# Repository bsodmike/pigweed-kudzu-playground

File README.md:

# Kudzu

[TOC]

## Getting Started

Make sure you've set up [Pigweed's
prerequisites](https://pigweed.dev/docs/getting_started.html#prerequisites).

**If you're on Windows**, you can automate the initial setup by downloading the
first-time setup script **from cmd.exe**:

```bat
curl https://pigweed.googlesource.com/pigweed/sample_project/+/main/tools/setup_windows_prerequisites.bat?format=TEXT > setup_pigweed_prerequisites.b64 && certutil -decode -f setup_pigweed_prerequisites.b64 setup_pigweed_prerequisites.bat && del setup_pigweed_prerequisites.b64
```

Then you can run the script with the following command **in cmd.exe**:

```bat
setup_pigweed_prerequisites.bat
```

Note: You may see a few UAC prompts as the script installs Git, Python, and
enables developer mode.

Once that is done, you can clone this project with the following command:
```sh
git clone https://pigweed.googlesource.com/pigweed/kudzu
```

### Environment setup

Pigweed uses a local development environment for most of its tools. This
means tools are not installed to your machine, and are instead stored in a
directory inside your project (Note: git ignores this directory). The tools
are temporarily added to the PATH of the current shell session.

To make sure the latest tooling has been fetched and set up, run the bootstrap
command for your operating system:

**Windows**

```bat
bootstrap.bat
```

**Linux & Mac**

```sh
source ./bootstrap.sh
```

After tooling updates, you might need to run bootstrap again to ensure the
latest tools.

After the initial bootstrap, you can use use the `activate` scripts to configure
the current shell for development without doing a full update.

**Windows**

```sh
activate.bat
```

**Linux & Mac**

```sh
source ./activate.sh
```

### Device tools setup

Install the pico SDK and tool to flash the device.

```sh
pw package install pico_sdk
pw package install picotool
```
These packages will be built and added to the path automatically. There is no
need to add these to the gn arguments.

## Linux Setup

### GLFW Dependency:

Install the GLFW OpenGL library
```sh
sudo apt install libglfw3-dev libglfw3
```

### Udev Rules:

Put the following into `/usr/lib/udev/rules.d/49-picoprobe.rules`

```
# Pico app mode
SUBSYSTEMS=="usb", ATTRS{idVendor}=="2e8a", ATTRS{idProduct}=="000a", MODE:="0666"
KERNEL=="ttyACM*", ATTRS{idVendor}=="2e8a", ATTRS{idProduct}=="000a", MODE:="0666", SYMLINK+="rp2040"

# RP2 Boot
SUBSYSTEMS=="usb", ATTRS{idVendor}=="2e8a", ATTRS{idProduct}=="0003", MODE:="0666"
KERNEL=="ttyACM*", ATTRS{idVendor}=="2e8a", ATTRS{idProduct}=="0003", MODE:="0666", SYMLINK+="rp2040"

# Picoprobe
SUBSYSTEMS=="usb", ATTRS{idVendor}=="2e8a", ATTRS{idProduct}=="0004", MODE:="0666"
KERNEL=="ttyACM*", ATTRS{idVendor}=="2e8a", ATTRS{idProduct}=="0004", MODE:="0666", SYMLINK+="picoprobe"
```

This will also symlink `/dev/picoprobe` and `/dev/rp2040` to the respective
vendor and product ids.

Apply the above rules with:

```sh
sudo udevadm control --reload-rules
sudo udevadm trigger
```

## Compile:

```sh
pw build
```

## Run:

### Host

Run the host app and connect to it via `pw-system-console`:

```sh
./out/gn/host_device_simulator.speed_optimized/obj/applications/badge/bin/badge & \
  pw-system-console --socket-addr default \
    --proto-globs third_party/pigweed/pw_rpc/echo.proto ; \
  killall badge
```

### Kudzu

```sh
export ELF=./out/gn/rp2040.size_optimized/obj/applications/badge/bin/badge.elf

picotool reboot -f -u && \
  sleep 3 && \
  picotool load -x $ELF
```

Connect with `pw-system-console`:

```sh
pw-system-console --verbose \
  --baudrate 115200 \
  --proto-globs third_party/pigweed/pw_rpc/echo.proto \
  --token-databases ./out/gn/rp2040.size_optimized/obj/applications/badge/bin/badge.elf \
  --device /dev/rp2040
```

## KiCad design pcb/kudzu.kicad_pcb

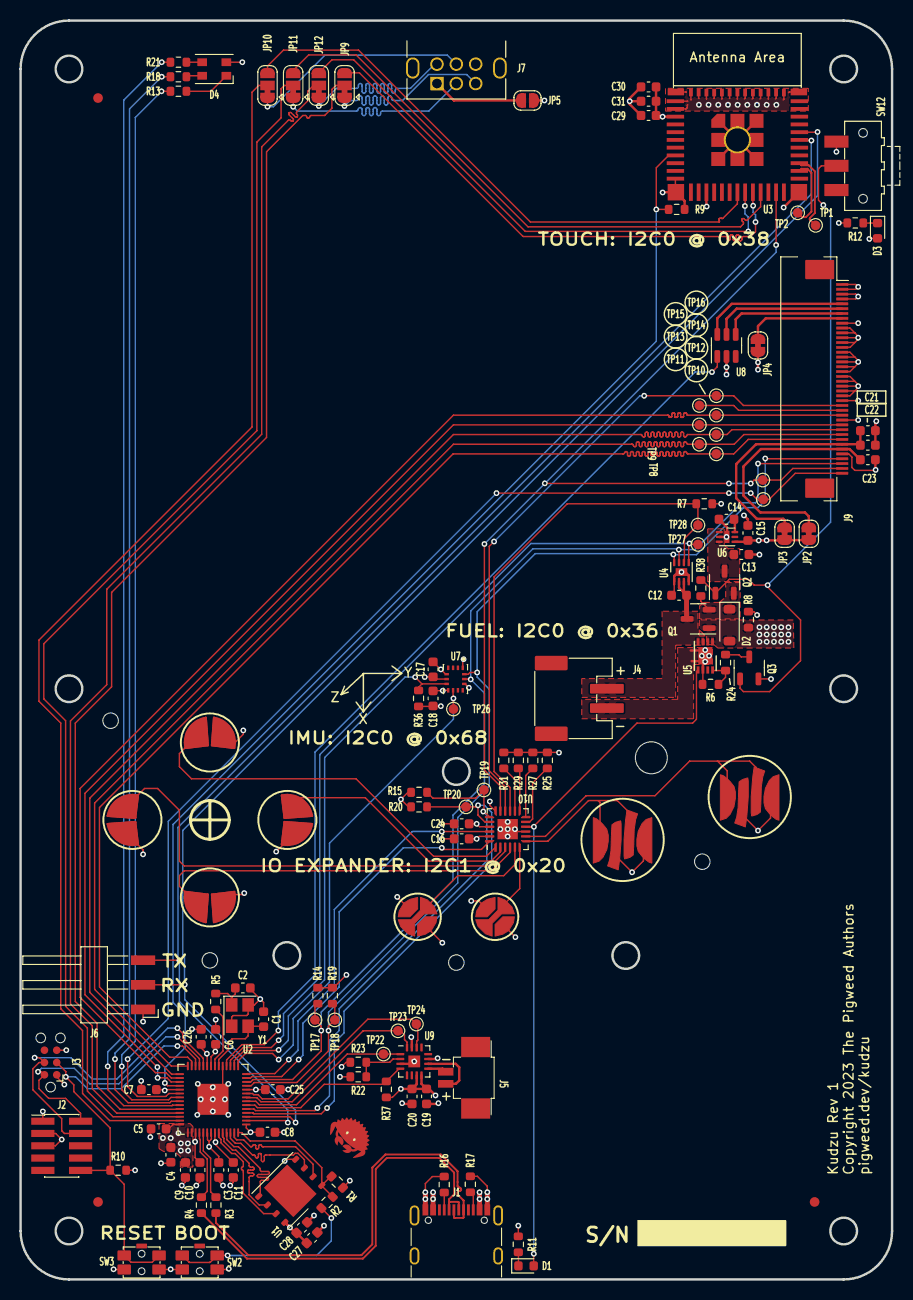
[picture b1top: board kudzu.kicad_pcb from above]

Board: 4 copper layers, 90.0 x 130.0 mm, 123 parts (0 on the bottom side), 102 nets.

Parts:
C1, C2: 27pF; C_0603_1608Metric
C3, C4, C5, C6, C7, C8, C11, C12, C14, C16, C18, C19, C22, C23, C24, C25, C26, C28, C31: 100nF; C_0603_1608Metric
C9, C10, C15, C27, C30: 2.2uF; C_0603_1608Metric
C13: 1uF; C_0603_1608Metric
C17, C29: 10nF; C_0603_1608Metric
C20, C21: 10uF; C_0603_1608Metric
D1: ORANGE; LED_0603_1608Metric
D2: D_Schottky; D_SOD-123
D3: GREEN; LED_0603_1608Metric
D4: LED_RABG; LED_Cree-PLCC4_3.2x2.8mm_CCW
J1: USB_C_Receptacle_USB2.0; USB_C_Receptacle_GCT_USB4105-xx-A_16P_TopMnt_Horizontal
J2: ARM 10 Pin SWD; PinHeader_2x05_P1.27mm_Vertical_SMD
J3: 6 Pin Tag Connect; Tag-Connect_TC2030-IDC-NL_2x03_P1.27mm_Vertical
J4: Conn_01x02; JST_PH_S2B-PH-SM_1x02_P2.00mm_Horizontal
J5: Conn_01x02; CONN HEADER SMD 2POS 1.25MM
J6: Conn_01x03; Harwin_M20-89003xx_1x03_P2.54mm_Horizontal
J7: GameBoy_LinkPort; GameBoy_LinkPort_MGB_Horizontal
J9: Conn_01x40_MountingPin; FPC-Connector_1x40-1MP_P0.50mm_Horizontal
JP2, JP3, JP4: SolderJumper_2_Bridged; SolderJumper-2_P1.3mm_Bridged_RoundedPad1.0x1.5mm
JP5: GBA_VDD; SolderJumper-2_P1.3mm_Open_RoundedPad1.0x1.5mm
JP9, JP10, JP11, JP12: SolderJumper_3_Bridged12; SolderJumper-3_P1.3mm_Bridged12_RoundedPad1.0x1.5mm
Q1, Q2: Q_PMOS_GSD; SOT-23-3
Q3: Q_NMOS_GSD; SOT-23-3
R1, R7, R8, R9, R10, R36, R38: 10K; R_0603_1608Metric
R2, R5: 1K; R_0603_1608Metric
R3, R4: 27R; R_0603_1608Metric
R6, R24: 4.02K 1%; R_0603_1608Metric
R11, R12: 1.5K; R_0603_1608Metric
R13: 280R 1%; R_0603_1608Metric
R14, R15, R19, R20: 3.3K; R_0603_1608Metric
R16, R17: 5.1K; R_0603_1608Metric
R18, R21: 60.4R 1%; R_0603_1608Metric
R22, R23: 100K; R_0603_1608Metric
R25, R27, R29, R31: 0; R_0603_1608Metric
R37: 634K; R_0603_1608Metric
SW1: AGB_DPAD; GBA_DPad
SW2: BOOT; SW_Push_1P1T_NO_CK_PTS840_GK_SMTR_LFS
SW3: RESET; SW_Push_1P1T_NO_CK_PTS840_GK_SMTR_LFS
SW4: AGB_AB; GBA_AB
SW5: AGB_SELECT_START; GBA_StartSelect
SW12: SW_SPDT; SW_SPDT_CK-JS102011SAQN
TP1, TP2, TP16: DISP_RESET; TestPoint_Pad_D1.0mm
TP8: TOUCH_IRQ; TestPoint_Pad_D1.0mm
TP9: TOUCH_RESET; TestPoint_Pad_D1.0mm
TP10: DISP_FMARK; TestPoint_Pad_D1.0mm
TP11: DISP_CS_N; TestPoint_Pad_D1.0mm
TP12: DISP_CLK; TestPoint_Pad_D1.0mm
TP13: DISP_D_C; TestPoint_Pad_D1.0mm
TP14: DISP_SDI; TestPoint_Pad_D1.0mm
TP15: DISP_SDO; TestPoint_Pad_D1.0mm
TP17: SENSOR_SCL; TestPoint_Pad_D1.0mm
TP18: SENSOR_SDA; TestPoint_Pad_D1.0mm
TP19: IO_SCL; TestPoint_Pad_D1.0mm
TP20: IO_SDA; TestPoint_Pad_D1.0mm
TP22: AUDIO_DATA; TestPoint_Pad_D1.0mm
TP23: AUDIO_BCLK; TestPoint_Pad_D1.0mm
TP24: AUDIO_LRCLK; TestPoint_Pad_D1.0mm
TP26: IMU_INT2; TestPoint_Pad_D1.0mm
TP27: GAUGE_ALERT_N; TestPoint_Pad_D1.0mm
TP28: GAUGE_QSTRT; TestPoint_Pad_D1.0mm
U1: W25Q128JVPIQ; WSON-8-1EP_6x5mm_P1.27mm_EP3.4x4.3mm
U2: RP2040; QFN-56-1EP_7x7mm_P0.4mm_EP3.2x3.2mm
U3: ESP32-C3-MINI-1; ESP32-C3-MINI-1_HandSoldering
U4: MAX17048; TDFN-8-1EP_2x2mm_P0.5mm_EP0.8x1.2mm
U5: MCP73831-MC; DFN-8-1EP_3x2mm_P0.5mm_EP1.75x1.45mm
U6: MIC5353-3.3YMT; MLF-6-1EP_1.6x1.6mm_P0.5mm_EP0.5x1.26mm
U7: ICM-42670-P; IC_ICM-42670-P
U8: AP2502; SOT-23-6
U9: MAX98357; TQFN-16-1EP_3x3mm_P0.5mm_EP1.23x1.23mm
U10: PI4IOE5V6416; TQFN-24-1EP_4x4mm_P0.5mm_EP2.1x2.1mm
Y1: 12 MHz; Crystal_SMD_3225-4Pin_3.2x2.5mm

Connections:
+1V1: C10.1, C11.1, C26.1, U2.23 (DVDD), U2.45 (VREG_VOUT), U2.50 (DVDD)
+3V3: C3.1, C4.1, C5.1, C6.1, C7.1, C8.1, C9.1, C15.1, C16.1, C17.2, C18.2, C19.1, C20.1, C24.1, C25.1, C27.1, C28.1, C29.1, C30.1, C31.1, D3.2 (A), D4.2 (A), J2.1 (VTref), J3.1 (VCC), J9.12, J9.39, J9.40, JP2.1 (A), JP3.1 (A), JP4.2 (B), JP5.1 (A), R1.2, R10.2, R14.2, R15.2, R19.2, R20.2, R22.2, R37.1, U1.8 (VCC), U2.1 (IOVDD), U2.10 (IOVDD), U2.22 (IOVDD), U2.33 (IOVDD), U2.42 (IOVDD), U2.43 (ADC_AVDD), U2.44 (VREG_IN), U2.48 (USB_VDD), U2.49 (IOVDD), U3.3 (3V3), U6.4 (VOUT), U7.5 (VDDIO), U7.8 (VDD), U7.12 (AP_CS), U9.7 (VDD), U9.8 (VDD), U10.21 (VDD_P), U10.23 (VDD_I2C)
+BATT: C12.2, J4.1, Q1.3 (D), U4.2 (CELL), U4.3 (VDD), U5.3 (BATT), U5.4 (BATT)
/RP2040 and Debug/QSPI_CLK: U1.6 (CLK), U2.52 (QSPI_SCLK)
/RP2040 and Debug/QSPI_CS_N: R1.1, R2.1, U1.1 (~CS), U2.56 (QSPI_SS)
/RP2040 and Debug/QSPI_SD0: U1.5 (DI(IO0)), U2.53 (QSPI_SD0)
/RP2040 and Debug/QSPI_SD1: U1.2 (DO(IO1)), U2.55 (QSPI_SD1)
/RP2040 and Debug/QSPI_SD2: U1.3 (IO2), U2.54 (QSPI_SD2)
/RP2040 and Debug/QSPI_SD3: U1.7 (IO3), U2.51 (QSPI_SD3)
/RP2040 and Debug/SWCLK: J2.4 (SWDCLK/TCK), J3.4 (SWCLK), U2.24 (SWCLK)
/RP2040 and Debug/SWDIO: J2.2 (SWDIO/TMS), J3.2 (SWDIO), U2.25 (SWD)
/RP2040 and Debug/USBD_N: J1.A7 (D-), J1.B7 (D-), R4.1
/RP2040 and Debug/USBD_P: J1.A6 (D+), J1.B6 (D+), R3.1
/misc/C3_MTCK: JP9.3 (B), U3.20 (GPIO6)
/misc/C3_MTDI: JP12.3 (B), U3.19 (GPIO5/ADC2_CH0)
/misc/C3_MTDO: JP11.3 (B), U3.21 (GPIO7)
/misc/C3_MTMS: JP10.3 (B), U3.18 (GPIO4/ADC1_CH4)
/misc/C3_USBD_N: TP2.1, U3.26 (GPIO18/USB_D-)
/misc/C3_USBD_P: TP1.1, U3.27 (GPIO19/USB_D+)
/power/POWER_SW_N: Q2.1 (G), Q3.1 (G), R38.1, SW12.2 (B)
/power/VSYS: C13.1, Q2.3 (D), U6.1 (EN), U6.3 (VIN)
/power/VSYS_ALWAYS: D2.1 (K), Q1.2 (S), Q2.2 (S), R38.2
/ux/BUTTON_A: SW4.2 (A), U10.8 (P0_7)
/ux/BUTTON_B: SW4.1 (B), U10.7 (P0_6)
/ux/BUTTON_DOWN: SW1.2 (DOWN), U10.4 (P0_3)
/ux/BUTTON_LEFT: SW1.3 (LEFT), U10.3 (P0_2)
/ux/BUTTON_RIGHT: SW1.4 (RIGHT), U10.2 (P0_1)
/ux/BUTTON_SELECT: SW5.1 (SELECT), U10.5 (P0_4)
/ux/BUTTON_START: SW5.2 (START), U10.6 (P0_5)
/ux/BUTTON_UP: SW1.1 (UP), U10.1 (P0_0)
/ux/DISP_IOVCC: C23.2, J9.6, JP2.2 (B)
/ux/DISP_LEDA: J9.33, JP4.1 (A)
/ux/DISP_LEDK_0: J9.34, U8.4 (LED3)
/ux/DISP_LEDK_1: J9.35, U8.5 (LED2)
/ux/DISP_LEDK_2: J9.36, U8.6 (LED1)
/ux/DISP_RESET: J9.15, TP16.1, U10.16 (P1_6)
/ux/DISP_SDO: J9.14, TP15.1
/ux/DISP_VCI: C21.2, C22.2, J9.7, JP3.2 (B)
/ux/GAIN_SLOT: R22.1, R23.2, U9.2 (GAIN_SLOT)
AUDIO_BCLK: TP23.1, U2.8 (GPIO6), U9.16 (BCLK)
AUDIO_DATA: TP22.1, U2.7 (GPIO5), U9.1 (DIN)
AUDIO_LRCLK: TP24.1, U2.9 (GPIO7), U9.14 (LRCLK)
AUDIO_SD: R37.2, U2.6 (GPIO4), U9.4 (SD_MODE)
BOARD_ID0: R25.2, U10.11 (P1_1)
BOARD_ID1: R27.2, U10.12 (P1_2)
BOARD_ID2: R29.2, U10.13 (P1_3)
BOARD_ID3: R31.2, U10.14 (P1_4)
C3_RESET_N: R9.1, U2.32 (GPIO21), U3.8 (EN/CHIP_PU)
CHARGE_STAT: D1.2 (A), U5.5 (STAT), U10.10 (P1_0)
DISP_BACKLIGHT: U2.18 (GPIO15), U8.1 (EN)
DISP_CLK: J9.10, TP12.1, U2.29 (GPIO18)
DISP_CS_N: J9.9, TP11.1, U2.28 (GPIO17)
DISP_D_C: J9.11, TP13.1, U2.31 (GPIO20)
DISP_FMARK: J9.8, TP10.1, U2.27 (GPIO16)
DISP_SDI: J9.13, TP14.1, U2.30 (GPIO19)
GAUGE_ALERT_N: TP27.1, U2.17 (GPIO14), U4.5 (ALRT)
GAUGE_QSTRT: R7.2, TP28.1, U4.6 (QSTRT), U10.15 (P1_5)
GBA_SC: J7.5 (SC), JP9.1 (A)
GBA_SD: J7.4 (SD), JP10.1 (A)
GBA_SI: J7.3 (SI), JP11.1 (A)
GBA_SO: J7.2 (SO), JP12.1 (A)
GND: C1.1, C2.1, C3.2, C4.2, C5.2, C6.2, C7.2, C8.2, C9.2, C10.2, C11.2, C12.1, C13.2, C14.2, C15.2, C16.2, C17.1, C18.1, C19.2, C20.2, C21.1, C22.1, C23.1, C24.2, C25.2, C26.2, C27.2, C28.2, C29.2, C30.2, C31.2, J1.A1 (GND), J1.A12 (GND), J1.B1 (GND), J1.B12 (GND), J1.S1 (SHIELD), J2.3 (GND), J2.5 (GND), J3.5 (GND), J4.2, J6.1, J7.6 (GND), J7.SH, J9.5, J9.16, J9.17, J9.18, J9.19, J9.20, J9.21, J9.22, J9.23, J9.24, J9.25, J9.26, J9.27, J9.28, J9.29, J9.30, J9.31, J9.32, J9.37, J9.38, Q3.2 (S), R6.1, R7.1, R8.1, R9.2, R11.1, R12.1, R16.2, R17.2, R23.1, R25.1, R27.1, R29.1, R31.1, R36.2, SW1.5 (COM), SW2.2, SW3.2, SW4.3 (COM), SW5.3 (COM), SW12.3 (C), U1.4 (GND), U2.19 (TESTEN), U2.57 (GND), U3.1 (GND), U3.2 (GND), U3.11 (GND), U3.14 (GND), U3.36 (GND), U3.37 (GND), U3.38 (GND), U3.39 (GND), U3.40 (GND), U3.41 (GND), U3.42 (GND), U3.43 (GND), U3.44 (GND), U3.45 (GND), U3.46 (GND), U3.47 (GND), U3.48 (GND), U3.49 (GND), U3.50 (GND), U3.51 (GND), U3.52 (GND), U3.53 (GND), U4.1 (CTG), U4.4 (GND), U4.9 (GND), U5.6 (VSS), U5.9 (VSS), U6.2 (GND), U6.7 (GND), U7.1 (AP_SDO/AP_AD0), U7.6 (GND), U8.2 (GND), U9.3 (GND), U9.11 (GND), U9.15 (GND), U9.17 (GND), U10.9 (VSS), U10.18 (ADDR), U10.25 (VSS), Y1.2, Y1.4
IMU_FSYNC: R36.1, U2.16 (GPIO13), U7.7 (FSYNC)
IMU_INT2: TP26.1, U2.15 (GPIO12), U7.9 (INT2)
IO_INT_N: U2.14 (GPIO11), U10.22 (INT)
IO_RESET_N: U2.13 (GPIO10), U10.24 (RESET)
IO_SCL: R15.1, TP19.1, U2.5 (GPIO3), U10.19 (SCL)
IO_SDA: R20.1, TP20.1, U2.4 (GPIO2), U10.20 (SDA)
unnamed: C2.2, R5.1, Y1.1
unnamed: D1.1 (K), R11.2
unnamed: D3.1 (K), R12.2
unnamed: D4.3 (BK), R21.2
unnamed: D4.4 (GK), R18.2
unnamed: D4.1 (RK), R13.2
unnamed: J1.A5 (CC1), R16.1
unnamed: J1.B5 (CC2), R17.1
unnamed: J5.1, U9.10 (OUTN)
unnamed: J5.2, U9.9 (OUTP)
unnamed: J7.1 (VDD), JP5.2 (B)
unnamed: Q3.3 (D), R24.1
unnamed: R4.2, U2.46 (USB_DM)
unnamed: R3.2, U2.47 (USB_DP)
unnamed: C1.2, U2.20 (XIN), Y1.3
unnamed: R5.2, U2.21 (XOUT)
unnamed: R6.2, R24.2, U5.8 (PROG)
unnamed: C14.1, U6.6 (BYP)
RESET_N: J2.10 (~RESET), J3.3 (~RESET), R10.1, SW3.1, U2.26 (RUN)
RP2040_SPI_CLK: JP9.2 (C), U2.38 (GPIO26_ADC0)
RP2040_SPI_CS: JP10.2 (C), U2.41 (GPIO29_ADC3)
RP2040_SPI_DI: JP11.2 (C), U2.40 (GPIO28_ADC2)
RP2040_SPI_DO: JP12.2 (C), U2.39 (GPIO27_ADC1)
SENSOR_SCL: J9.3, R14.1, TP17.1, U2.12 (GPIO9), U4.7 (SCL), U7.13 (AP_SCL/AP_SCLK)
SENSOR_SDA: J9.4, R19.1, TP18.1, U2.11 (GPIO8), U4.8 (SDA), U7.14 (AP_SDA/AP_SDIO/AP_SDI)
STATUS_B: R21.1, U2.37 (GPIO25)
STATUS_G: R18.1, U2.36 (GPIO24)
STATUS_R: R13.1, U2.35 (GPIO23)
TOUCH_IRQ: J9.1, TP8.1, U2.34 (GPIO22)
TOUCH_RESET: J9.2, TP9.1, U3.23 (GPIO9), U10.17 (P1_7)
UART_RX: J6.2, U2.3 (GPIO1), U3.31 (GPIO21/U0TXD)
UART_TX: J6.3, U2.2 (GPIO0), U3.30 (GPIO20/U0RXD)
USB_BOOT_N: R2.2, SW2.1
VBUS: D2.2 (A), J1.A4 (VBUS), J1.A9 (VBUS), J1.B4 (VBUS), J1.B9 (VBUS), Q1.1 (G), R8.2, U5.1 (VDD), U5.2 (VDD)

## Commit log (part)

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2023-08-31 Initial empty repository
2023-09-12 pcb: Add back art and qr code footprints
    Reviewed-on: https://pigweed-review.googlesource.com/c/pigweed/kudzu/+/170244
    Reviewed-by: Anthony DiGirolamo <tonymd@google.com>
2023-09-19 Update submodules
    - Switch to importing pigweed-experimental modules.gni
    - Remove picotool from bootstrap. It requires libusb on the host
    machine which can fail on MacOS and Windows.
    Reviewed-on: https://pigweed-review.googlesource.com/c/pigweed/kudzu/+/171772
    Reviewed-by: Erik Gilling <konkers@google.com>
2023-10-06 Update Rp2040DigitalInOut calls
    Reviewed-on: https://pigweed-review.googlesource.com/c/pigweed/kudzu/+/174970
    Reviewed-by: Armando Montanez <amontanez@google.com>
2023-10-09 Move random functions to a reusable library
    Reviewed-on: https://pigweed-review.googlesource.com/c/pigweed/kudzu/+/174971
    Reviewed-by: Armando Montanez <amontanez@google.com>
2023-10-19 OWNERS: Include Pigweed OWNERS
    Reviewed-on: https://pigweed-review.googlesource.com/c/pigweed/kudzu/+/176787
    Reviewed-by: Anthony DiGirolamo <tonymd@google.com>
    Commit-Queue: Rob Mohr <mohrr@google.com>
2023-10-20 [third_party/pigweed] Roll 2 commits
    16d9aa7b128ef89 pw_bluetooth: Define LEChannelSelectionAlgorithmSu
    e539a0b0def3b6a pw_bluetooth: Define LEScanTimeoutSubevent
    https://pigweed.googlesource.com/pigweed/pigweed
    third_party/pigweed Rolled-Commits: f5540e6a1c3bf0b..16d9aa7b128ef89
    Roller-URL: https://ci.chromium.org/b/8766763420531090769
    GitWatcher: ignore
2023-10-22 [roll third_party/pigweed] roll: gn
    From: git_revision:182a6eb05d15cc76d2302f7928fdb4f645d52c53
    To: git_revision:5d8727f3fbf420538ff753ebc3ce96da28e12c22
    Original-Reviewed-on: https://pigweed-review.googlesource.com/c/pigweed/pigweed/+/177330
    Bot-Commit: Pigweed Roller <pigweed-roller@pigweed-service-accounts.iam.gserviceaccount.com>
    https://pigweed.googlesource.com/pigweed/pigweed
    third_party/pigweed Rolled-Commits: 45fbd96e68ce3eb..8c8719939903452
2023-10-25 [roll third_party/pigweed] pw_rpc: Support DynamicClient with SynchronousCallFor API
    - Add support of using DynamicClient with SynchronousCallFor API
    Original-Fixes: b/296873594
    Original-Reviewed-on: https://pigweed-review.googlesource.com/c/pigweed/pigweed/+/177637
    https://pigweed.googlesource.com/pigweed/pigweed
    third_party/pigweed Rolled-Commits: 62da7d49d272099..ae1e90eb632000a
    Roller-URL: https://ci.chromium.org/b/8766305998137666449
2023-10-25 [roll third_party/pigweed] Bazel: Remove most copts from pw_cc_library macro
    Putting the copts in the macro was a workaround while we didn't control
    our compiler configuration.
    The warnings flags need to stay here until b/300330623 is fixed. The
    problem is that our dependencies trip these warnings, so we can't apply
    them at the toolchain level.
    Original-Bug: b/267498492
2023-10-27 [roll third_party/pigweed] pw_build: Remove pw_build_default_configs_in_toolchain
    Removes the last remnant of the GN default config handling cleanup.
    Original-Fixes: b/260111641
    Original-Reviewed-on: https://pigweed-review.googlesource.com/c/pigweed/pigweed/+/177894
    https://pigweed.googlesource.com/pigweed/pigweed
    third_party/pigweed Rolled-Commits: f50e8aa47fdcf24..9aa8a037d67ac4f
    Roller-URL: https://ci.chromium.org/b/8766057367556539617
2023-11-01 [third_party/pigweed] Roll 4 commits
    050c2211536b89e pw_build: Add empty_cc_library
    cde4af63efd7b35 pw_{log,protobuf,tokenizer}: Enable sandboxing for
    54bd48f7fa02550 docs: Add udev instructions to Bazel Get Started
    1c95672718137e0 docs: Add information on the experimental repo to
    https://pigweed.googlesource.com/pigweed/pigweed
    third_party/pigweed Rolled-Commits: dd7d1407ce51298..050c2211536b89e
2023-11-14 [third_party/pigweed] Roll 8 commits
    1548f2406f69d61 bazel: Upgrade nanopb version
    8a42e20a49f2810 bazel: Use Python 3.11
    6ec8e692dc12eac pw_transfer: Limit data sent in manual cancel test
    32e50427e7ff68e pw_console: Add docs banner
    7fa35463d77e315 bazel: Update comment
    effa6cb1c98d9f3 pw_system: Add tracing to the demo system
2023-11-30 [third_party/pigweed] Roll 24 commits
    b4e82abda1f7785 pw_multibuf: Make HeaderChunkRegionTracket public
    a5da9446fb2c7f6 pw_unit_test: Skip googletest tests if not set
    5a521cb4f24cfd6 docs: Gerrit code coverage documentation
    db39d89da115738 docs: Move copyright header info to style guide
    7afbb205c205659 pw_allocator: Fix use-after-free in ~AllocatorForT
    8750debc3c31d37 pw_presubmit: Fix TestTodoCheck.test_one_bug_legac
2023-12-18 [third_party/pigweed] Roll 7 commits
    afcd5733cf2bed9 roll: gn
    f8c71146b855fd8 docs: Update changelog
    5b32d8dc55c9ac1 pw_async2: Fix documentation style
    2a2b4ff0002535d pw_transfer: Minor python improvements
    78a0fc76e94c7db pw_web: Add tests for Log Source and log handling
    50a77aa8bbe1c8e pw_bluetooth_sapphire: Read ISO data buffer info o
2024-01-05 [third_party/pigweed] Roll 10 commits
    a8c971304f5c6f5 zephyr: Link pw_thread.sleep with appropriate kCon
    b8242a102440067 pw_allocator: Add note to AllocatorMetricProxy tes
    fed83a673aa0630 pw_emu: Remove psutil dependency
    8d9da580a07cba7 bazel: Remove pw_cc_library
    af9badd2ffc93c0 pw_protobuf: Fully qualify message namespace
    d7660411ec0d621 pw_env_setup: Use correct arch for cipd in Bazel
2024-01-22 [third_party/pigweed] Roll 13 commits
    0380161bd68c216 roll: gn
    ee7c25d76da067d roll: 310, 311, 38, 39
    367c357d0886c41 roll: bazel
    6fc6f6debcbae24 pw_ide: Fix typo
    858c1dd3b1e55a1 docs: Auto-generate module source code and issues
    b2a685f4fcbe72f pw_bytes: Make _b literals error on values >255
2024-02-08 [third_party/pigweed] Roll 12 commits
    81242b0406fd717 pw_allocator: Add BlockAllocator
    a7e8a40c06c2ee5 pw_toolchain_bazel: Implement per-action files
    e821637464c104e pw_allocator: Fix SynchronizedAllocator typo
    ba81124ae9b1e92 pw_env_setup: Roll cipd
    36a249c883d7ccb pw_config_loader: Initial commit
    9624e0c4a793753 pw_cli: Add json_config_loader_mixin
2024-02-14 [third_party/pigweed] Roll 12 commits
    7a40804002b6802 pw_presubmit: Fix formatting of typescript code
    a10cefdae71c520 docs: Fix 404s
    f5dd358055f255f pw_bluetooth: Update emboss imports to match Bazel
    8ed38666b8b7fdd pw_tokenizer: Proto migration stage 3/5
    77cba4c16866ec4 pw_presubmit: Disallow FIXME and recommend TODO
    b3903d8ab6c36b8 bazel: Upgrade protobuf to 4.24.4
2024-02-23 [third_party/pigweed] Roll 3 commits
    e8c65f4cc0c1568 pw_allocator: Remove total_bytes metric
    a5038affded6fea docs: Add breadcrumbs
    97f12d317d2ef3d Revert "roll: clang"
    https://pigweed.googlesource.com/pigweed/pigweed
    third_party/pigweed Rolled-Commits: 5165b9c17a9933b..e8c65f4cc0c1568
    Roller-URL: https://ci.chromium.org/b/8755313872934545425
2024-03-12 [third_party/pigweed] Roll 14 commits
    8160a4da123eb03 pw_allocator: Move code snippets from docs to exam
    c66b857f68439ac roll: clang
    543f721f41dee53 docs: TOC entry for API documentation from source
    e4881d6811941cb pw_allocator: Clean up sources files
    4bfff95481ee895 pw_log: Run bpfmt on all Android.bp
    1a4757dd7737821 bazel: Fix bazel query
2024-03-25 [third_party/pigweed] Roll 2 commits
    c6c4a5bbeef2f11 roll: gn
    dabe438c436d688 roll: 310, 311
    https://pigweed.googlesource.com/pigweed/pigweed
    third_party/pigweed Rolled-Commits: bb8031432ff42f7..c6c4a5bbeef2f11
    Roller-URL: https://ci.chromium.org/b/8752505369302252865
    GitWatcher: ignore
2024-04-05 [third_party/pigweed] Roll 6 commits
    517696e29810c51 docs: Mention that Windows flow needs admin rights
    849d99bd97a5613 pw_presubmit: Include examples repo docs in docs_b
    3f89c18fdffd43f pw_module: Jinja template refactor
    6222b1097d11fb1 docs: Update reST style guide
    c68babc5337f950 pw_async2: Add Poll::Readiness helper
    ef7a6d3ac854bea pw_toolchain: Fix Rust GN host build
2024-04-23 [third_party/pigweed] Roll 14 commits
    c6e83c173d13b52 pw_tokenizer: Support arbitrary recursion in C++ d
    8d915ae182f1a1f docs: Update module docs contributor guidelines
    682ac383f108edd emboss: Update emboss repo to tag v2024.0419.15560
    b21f1b705dbf644 pw_web: Add user guide page for features and filte
    9a0e93fe506c9f5 *: Replace `string_view&` with `string_view`
    1e8d9d0656f836f docs: Add GitHub pull request template
2024-05-08 [third_party/pigweed] Roll 11 commits
    258066a475ea2cf pw_libcxx: Minimal implementation
    188876aa96f12be pw_format: Add Rust support for formatting integer
    95093534642cccc pw_bluetooth_proxy: Add cmake build rules
    8cdcad7cc37aefa pw_{rpc,trace_tokenized}: Build compatibility fixe
    a1802f8bb4e2c92 pw_protobuf_compiler: Disable layering_check
    4f0b1a7c4cd2ee2 pw_format: Add test for escaped curly brackets
2024-05-24 [third_party/pigweed] Roll 9 commits
    e0af1981782a05e targets/rp2040: Enable thread high water accountin
    8c1118fc91c259d rp2040: Renable tests that pass with larger stack
    2ee9bbd280bae2f pw_web: Add split/resize view guide in docs
    a90dc693295df7a pw_web: Implement split log views with resize
    37233cc5c5bdc8d pw_unit_test: Don't execute multiple test suites a
    f80cb7eb38f8b1a pw_grpc: Fix warnings in format strings
2024-06-04 [third_party/pigweed] Roll 15 commits
    6618a7d3265639b pw_chrono: Introduce SystemClock backed link time
    d988f7027fe939e pw_env_setup: Bootstrap fish-shell support
    d91003238d9cf8b pw_ide: Fix constant Pylance crashes
    80a5042814f199d pw_thread_freertos: Expand comment to help when de
    9bed7bf6daedb3b pw_channel: Update function documentation
    4cf2d05a70b44da pw_multibuf: Fix Truncate(0) on empty MultiBuf
2024-06-14 roll: third_party/pigweed 2 commits
    a200b716cd13652 pw_rpc: Restructure Channel / internal::Channel
    8a07d9f1ce8b58f pw_allocator: Clean up Block interface
    https://pigweed.googlesource.com/pigweed/pigweed
    third_party/pigweed Rolled-Commits: 17c1ee08b087155..a200b716cd13652
    Roller-URL: https://ci.chromium.org/b/8745130855380197665
    GitWatcher: ignore
2024-07-02 Display and FreeRTOS fixes
    - Rename FreeRTOS port handler functions.
    - Add missing screen width and height members to display driver config.
    Reviewed-on: https://pigweed-review.googlesource.com/c/pigweed/kudzu/+/219421
    Lint: Lint 🤖 <android-build-ayeaye@system.gserviceaccount.com>
    Commit-Queue: Anthony DiGirolamo <tonymd@google.com>
    Reviewed-by: Armando Montanez <amontanez@google.com>
2024-07-16 roll: third_party/pigweed 24 commits
    789f3ef5abc6b6e pw_{kvs,stream}: Update bazel config
    8f327bb620173a2 pw_toolchain: Pico Bazel build
    1bd9a79e9b80068 pw_ide: VSC status bar item for target selection
    2955c4c9a1a048b pw_toolchain: Add tsan support for host builds
    0e7b3303a2e5b35 pw_console: Replace placeholder page with real web
    a053780de153eee pw_web: NPM version bump to 0.0.20
2024-07-31 roll: third_party/pigweed 9 commits
    b454ef6a4541f4f pw_ide: Automatically activate Bazelisk in new ter
    ac59830dcdbd32c pw_system: Add console device aliases for common R
    b0153387ffcae11 pw_clock_tree_mcuxpresso: Introduce ClockMcuxpress
    ed88d9b037da70c pw_presubmit: Allow fxbug.dev and crbug.com TODOs
    513f5005834264d pw_transfer: Add a delay after opening a stream to
    b313a19ee2da2e9 pw_web: Change severity to level

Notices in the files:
pcb/kudzu.kicad_pcb:
Copyright 2023 The Pigweed Authors
